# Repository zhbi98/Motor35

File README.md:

# Motor35

转速-扭矩特性步进电机运用普通的开环控制方式在低速和低负载的情况下可以保持较好的控制精度，但随着负载增大或转速度增加会发生丢步，另一个是转速-扭矩特性让步进电机无法在高转速下稳定工作。

## 特性

在低速状态下，步进电机的扭矩特性曲线通常为水平直线，能够提供较高的扭矩。在高速状态下，由于电感的影响，扭矩特性曲线呈指数下降，导致电机的负载能力显著降低。

> **最大扭矩：** 最大扭矩出现在中低转速范围，随着转速的提高，扭矩会逐渐下降。因为在高频率下，电流流动受到绕组电感的影响，导致电流无法达到稳定值，从而扭矩降低。
> 
> **启动扭矩与连续扭矩：** 启动扭矩指在启动时能够提供的最大扭矩，而连续扭矩则指电机持续运行时能够维持的扭矩。随着脉冲频率的增加，启动扭矩和连续扭矩都会下降。

## 闭环

闭环控制是在开环控制的基础上，增加了 **反馈检测环节**（例如在电机轴增加编码器），形成指令-执行-位置检测-修正的闭环逻辑。解决存在的丢步、偏差、抗干扰能力弱问题，还能提升系统和容错能力。

## FOC 控制

混合式步进电机与无刷电机的内在联系（结构定义相似性，工作原理相似性），所以可以用无刷电机 FOC 的驱动思想驱动步进电机。

结构方面：永磁转子+定子绕组的结构，定子方面：两者都有多相绕组（步进电机通常为两相，无刷电机通常为三相），转子方面：都采用永磁材料制造转子磁极，无刷设计：两者都没有电刷和机械换向器，依靠电子换向。

对于两相步进电机，虽然只有两个绕组，但通常两相绕组是正交的，从而可以简化步骤，省略我们的 clarke 变换，所以其余同样可以采用类似的思路进行一个电流环FOC控制。

    电流检测：对 AB 两相电流进行检测
    Park变换：将 AB 轴静止系转换为dq轴旋转坐标系
    PI调节器：对 Id 和 Iq 进行控制
    Invpark变换：讲 dq 轴转换为AB轴
    SVPWM调制: 输出占空比
    双 H桥驱动：驱动我们的步进电机

这些可以整合到一个驱动器中实现，如下图。这就是一体化集成步进电机闭环驱动器。板上集成磁编码器，具有速度，位置，电流闭环控制功能，适用于 3D 打印机，小型机械臂。

## 硬件

(1) 2 相逆变功率级：东芝凌耐压 50V，载流3.5A 的 PWM 斩波式双全桥电机驱动器，内置带低导通电阻的输出MOSFET（基于成本考虑可以选择其他的型号）。

(2) RS485 收发器：TI 德州仪器 SN75176B（基于成本考虑可以选择其他的型号）。

(3) CAN2.0B 收发器：NXP 恩智浦 High-speed CAN transceiver TJA1051（基于成本考虑可以选择其他的型号）。

(4) 磁编码器：MagnTek 麦歌恩 mt6816 单圈绝对式14位编码器，支持最高转速25Krpm。

(6) 主控 MUC 芯片：意法半导体 STM32F103。

## 关于打样

驱动器板 Motor35（PCB 采用 **4 层板** 设计）：[HardWare/kiacd_project](./HardWare/kiacd_project)

如果想自己修改 PCB 需要安装 KiCad（开源的 EDA 工具，也非常易学），官方下载地址： https://www.kicad.org/。

打样制作可以直接进入到下面这两个路径下：

把 Motor35 Gerber 文件夹 [HardWare/Gerber](./Docs/Motor35-PCB/) 压缩为 Motor35.zip，

把这个 .zip 给 PCB 制造厂即可（例如 JLC，**PCB 经过打样验证，可以放心使用**）。

**器件 BOM 目录**：[HardWare/ibom.html](./Docs/Motor35-BOM.csv)（PCB 没器件位号，按网页交互式 BOM 贴片）。

原理图 PDF 目录： [Docs/Motor35-SCH.csv](Docs/Motor35-SCH.pdf)

## 核心固件

固件主要包括几大功能模块：

- hal 驱动：板载的各种硬件驱动比如 USB、Tim、Can、Spi。
- utils 库：STM32 的 Flash 存储接口，Modbus 协议解析库，软定时器组件。
- drivers：ARM的CMSIS驱动，ST官方的HAL库。
- device：电机H桥驱动，编码器驱动和校准，电机控制核心代码，LED 驱动框架 LedMX 和按键驱动 MultiButton。
- main：上层 Can，Rs485 应用控制协议，用于控制同步电机状态/参数，以及用户设置参数保存功能。

## 编译下载

固件没有使用 ARM Keil 开发，而是先用 CMake 构建出 Makefile，然后再用 arm-gcc 编译（可以自己创建 F103 的 Keil 工程，把 Motor35 组织到 Keil 编译）。

Motor35 用的是 VSCode 搭配 OpenOCD 图形化下载调试，需要下载安装下列工具链：

MiniGW： https://sourceforge.net/projects/mingw-w64/files/

arm-gcc ：[Downloads | GNU Arm Embedded Toolchain Downloads – Arm Developer](https://developer.arm.com/downloads/-/gnu-rm)

openOCD：[Download OpenOCD for Windows](https://gnutoolchains.com/arm-eabi/openocd/)

CMake：[Download CMake](https://cmake.org/download/)

VSCode：[https://code.visualstudio.com/](https://code.visualstudio.com/)

> 安装后具体如何配置使用这些工具，篇幅较长不写在这里，我把具体配置使用方法写在这里：[工具链配置使用方法](https://blog.csdn.net/jf_52001760/article/details/126826393)。

**Motor35 编译步骤**：

把 cmake 脚本 CMakeLists.txt 的目录添加到 `1` 这里，如下图。

(2) 在 Firmware 目录下创建 build 目录，并指定到 `2` 这里。

(3) 点击 "Configure"，在弹出面板选择目标工程，如下图。

(5) 在 vscode 的命令行 `cd build` 进入`build/`目录，然后执行 make -j2 即可开始编译。

(6) 使用 openOCD 把 `.elf` 文件下载到 Motor35 硬件，下载方法同样参照 [工具链配置使用方法](https://blog.csdn.net/jf_52001760/article/details/126826393)（PCB 上预留了 SWD 调试接口同时支持固件下载）。

## 电机选型

电机可以在淘宝搜索购买，最好购买低相电阻步进电机（较好的电机的相电阻通常为 2-5 Ohm）。相电阻过高可能导致电机在静止时出现高频震动。

电机机身：28MM，出轴直径：5MM (D轴4.5MM)，出轴长度：22MM
静力矩：0.29 N.m，额定电流：1.5 A，电阻：3.0Ohm/相。

> 要实际测量电机相电阻（万用表接到对应相的两个端子测量），比如购买的步进电机在参数描述中标明的相电阻为 2.2 Ohm，实则实际测出的相电阻高达 29 Ohm
> 
> 

## 编码器安装

在电机轴上安装径向磁铁（用于磁编码器检测），磁铁尺寸 $d=8mm$，$h=2mm$，注意径向磁铁和轴同心度不要过度偏移，让后把驱动器板放到板支架中，用 M3.0 螺丝把驱动器和板定到电机尾部，磁铁与编码器的间隙大概为 $1mm$。

驱动板支架零件目录：[Model](./Model)，把 .step 文件给 3D 打印即可。

## Configuration

固件上已经调试好 Pid 参数，可以适配大多数35步进电机，默认情况下不需要再调试 Pid 电机也能正常工作。Pid 可以用 Can 指令调整（看Can协议部分的说明），方法如下：

- **Kp 的调整**：将 Kd，Ki 置 0，从零开始逐渐增加 Kp，直到系统出现震荡。然后逐渐减小Kp，直到系统不再震荡。Kp 的最终值通常在引起震荡的 Kp 值的 80%-90% 之间。

- **Kd 的调整**：在 Kp 调整稳定后，开始增加 Kd。如果系统在空载时仅需要 Kp，那么在负载情况下可能需要增加 Kd 来减少超调和震荡。

- **Ki 的调整**：如果系统在 Kp 和 Kd 的调整后仍然存在静态误差，可以尝试增加 Ki。但 Ki的值通常很小，需要细致地调整。

配置限制参数，限制参数再 /motor/control_config.h 文件定义，如下。

```c
/********************  硬件配置区  ********************/
#define _Current_Rated_Current  (3000)  /**< 额定电流(mA)*/
#define _Current_Cali_Current   (2000)  /**< 校准电流(mA)*/
/********************  运动参数配置区  ********************/
...
#define _Move_Rated_Speed           ((int32_t)(50 * Move_Pulse_NUM))    /**< (额定转速)(50转每秒)*/
#define _Move_Rated_UpAcc           ((int32_t)(1000 * Move_Pulse_NUM))  /**< (固件额定加速加速度)(1000r/ss)*/
#define _Move_Rated_DownAcc         ((int32_t)(1000 * Move_Pulse_NUM))  /**(固件额定减速加速度)(1000r/ss)*/
#define _Move_Rated_UpCurrentRate   ((int32_t)(20 * _Current_Rated_Current))    /**< (固件额定增流梯度)(20倍额定/s)*/
#define _Move_Rated_DownCurrentRate ((int32_t)(20 * _Current_Rated_Current))    /**< (固件额定减流梯度)(20倍额定/s)*/
```

用户设置在 /main/setup/setup.c 中定义，用户设置参数可以用 Can 指令设置（看Can协议部分的说明）设置后保存在 Flash 掉电保存。

```c
const _setup_t _setup_def = {
    ...
    .can_id = 0x01,
    .home_ofs = 0,
    ...
    .current_down_acc = 2 * 1000, /*(mA/s)*/
    .current_up_acc = 2 * 1000, /*(mA/s)*/
    .current_rated = 1000,
    .cali_current = 2000,
    ...
};
```

## 按键逻辑

(1) 启动停止闭环模式：按键 1 短按一次，启动或停止闭环模式，启动闭环模式的同时会进入默认的模式，例如位置闭环。

(2) 目标清 0：按键 2 短按一次，如果当前控制模式为速度模式，那么按下此时会将目标速度置为 0，位置模式，则将目标位置置为 0。

(3) 电机编码器校准：按键 1 长按两次，校准时电机会慢速正转一圈再反转一圈。

> 按下按键时 LED 跟随闪烁，以指示按键是否响应。

## CAN 协议

一帧 CAN 报文只能传 8 个字节数据，和 11 位的标准 Std-Id，这里把 Std-Id 的低 7 位也用作数据，用来传控制指令字 CMD，控制协议定义如下：

Device Id 占用 4 位，CMD 占用 7 位，协议最多两个参数：参数 1 占用 4 个字节，参数 2 占用 4 个字节。

> 个别协议要两个参数，例如位置控制：设置目标位置和速度限制。

具体指令在[protocols/can_protocol.c](./Firmware/main/protocols/can_protocol.c) 这里定义，具体可以看这个文件，具体控制指令和控制方式查看 [Docs/Protocols](./Docs/Protocols) 目录下相应的协议文档，这里只截取部分。

## 震动问题

注意步进驱动器控制步进电机工作在位置环并要求静止在某个固定位置时可能会出现高频震动的问题。引起高频微弱震动的原因是由于在位置环控制模式下，驱动器为了让让电机接近指定位置而控制电机在齿槽间反复微调而产生震动。

> 这个现象排除驱动器的电路问题（比如焊接的电流采样电阻是否正确等等），磁编码器检测磁铁的安装同心度问题（通常同心度要求不是很高，确保不要过度偏移即可）那有极大的可能是步进电机的相电阻过大导致的，可以更换了其他电机进行测试。

如果更换电机测试后发现同一个闭环步进电机驱动器驱动一个步进电机工作在位置环保持静止时工作正常，而驱动另一个步进电机静止时出现高频震动，那可以肯定就是相电阻过高而导致的。出现震动现象的电机相电阻通常为 10-30 Ohm，而较好电机的相电阻通常为 2-5 Ohm。注意检查电机参数可能的虚标，例如购买的步进电机在参数描述中标明的相电阻为 2.2 Ohm，实则实际测出的相电阻高达 29 Ohm，所以电机出现震动现象和线圈相电阻是有一定关系的。

可以通过修改驱动器程序固件来修复这个问题，修改驱动输出部分，在最终 FOC 输出驱动电流部分添加一个系数即可，通过该系数来调节驱动器 FOC 的输出电流（当然调节电流参数会对最终的扭矩有略微的影响，但并不影响闭环精度），如下图。

## 控制带宽

电机控制速度/位置积分需要精确节拍，电机控制所有逻辑都是在定时器触发的中断中进行，我设置的中断函数频率较高，达到20KHz，可能会导致 main 主循环不执行。

> **20 kHz 中断**：TIM 每 50 μs 触发一次中断。

**电机控制逻辑较多：** 运行时间合计接近或超过 50 μs，会形成中断几乎连轴转、主循环几乎没机会跑”的情况（和芯片主频无关，只要中断内处理的时间超过中断周期时间就会导致 main 函数不执行）。

> 通过 SPI 阻塞读 MT6816，最多 3 次尝试 × 2 次 16bit 传输，再加 16 位奇偶校验循环。SPI 时钟为 9MHz，仅通信就可能 5-15μs。
> 
> 编码器处理、位置/速度估计、多种运行模式下的控制（DCE/PID/电流等）、运动规划、软目标更新、堵转/过载检测等就需要数十μs。

没有具体要求需要多少控制频率，控制制带宽越高，控制越平滑所以默认设定为 20KHz，若控制带宽允许，可把闭环控制改为 10 kHz 或 5 kHz，中断周期变为 100 μs / 200 μs。

> 这里 20 kHz 不是控制带宽的硬性要求，更多是裕量和步进分辨率。

修改控制频率同时改两处：
motion_planner.h 的  CONTROL_FREQUENCY 定义。
修改电机控制运行中断定时器的中断时间。

```c
/****************************************  控制器频率配置区  ****************************************/
#define CONTROL_FREQ_HZ   (20000)                     /**< 控制频率_hz*/
#define CONTROL_PERIOD_US (1000000 / CONTROL_FREQ_HZ) /**< 控制周期_us*/
```

### 评估控制带宽

(1) motor_control.c 涉及的一阶滤波：由 `等效时间常数由 >> 5`（约 32 个采样）决定。20 kHz 时：32 × 50us =1.6 ms 即控制带宽约 100 Hz。对很多应用来说 50 Hz 左右就足够。

(2) 位置/速度环 (DCE、PID 闭环带宽)：这是外环（位置环、速度环），一般做到几十到一两百 Hz 带宽就足够（位置/速度环 -3 dB 带宽）。 

> 常见经验：**采样率 ≥ 10～20 倍闭环带宽**。 
> 若你目标闭环带宽在 100～200 Hz，**5 kHz 已经够用，2 kHz 是底线**。

(3) FOC/电流指令：由 TB67H450 等驱动接收，5～10 kHz 更新电流给定对多数应用足够。

(4) 运动规划：用 CONTROL_FREQUENCY 做离散积分，频率高一点更平滑，但 5～10 kHz 通常足够平滑。

(5) 控制更新频率：下限约 2～5 kHz（再低速度估计和环路的相位裕量会变差）。推荐 5～10 kHz 在保证控制性能的同时，能给主循环留出明显时间。在需要 **极高步进率** 或 **尽量小的相位延迟** 时才必要 20 kHz。

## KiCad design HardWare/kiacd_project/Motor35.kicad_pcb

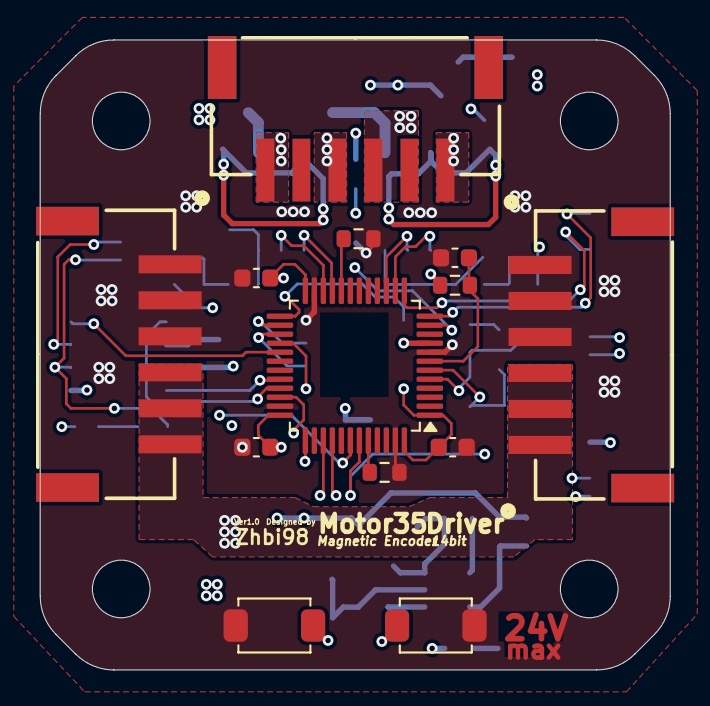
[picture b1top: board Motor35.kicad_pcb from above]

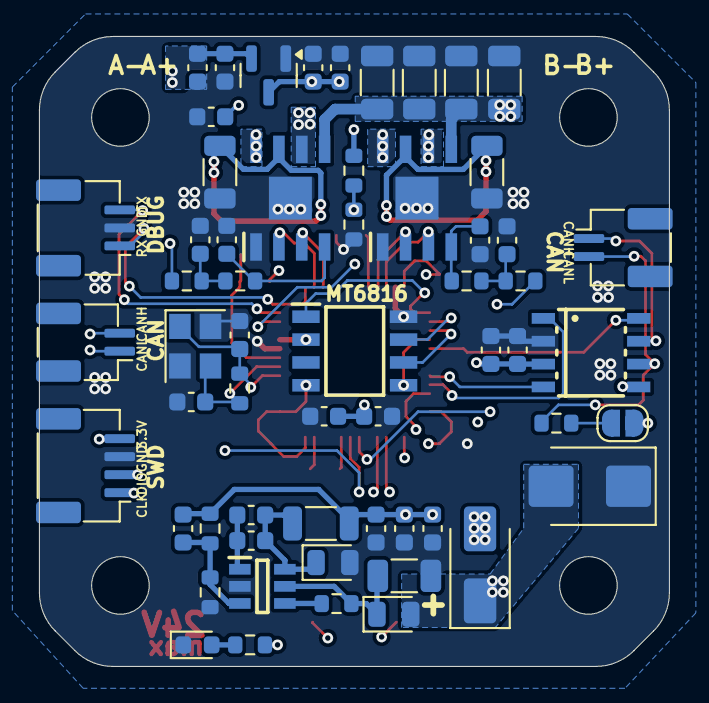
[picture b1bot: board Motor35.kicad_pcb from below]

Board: 4 copper layers, 35.0 x 35.0 mm, 71 parts (58 on the bottom side), 49 nets.

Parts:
C1, C3, C5, C7, C10, C11, C16: 0.1uF; C_0603_1608Metric
C2, C6: 22pF; C_0603_1608Metric
C4, C8, C17, C26, C31: 10uF; C_0603_1608Metric
C12, C13, C14, C15: 100nF (104) 10% 50V; C_0603_1608Metric
C18: 100pF(101) 50V; C_0603_1608Metric
C19, C20: 100nF(104) 50V; C_0603_1608Metric
C21: 100nF104; C_0603_1608Metric
C22: 4.7uF(475) 50V; C_1206_3216Metric
C23: 10uF(106); C_0603_1608Metric
C24: 47uF(106); C_0603_1608Metric
C27, C28, C29, C30: 100uF 50V; C_1206_3216Metric
C32: 100nF; C_0603_1608Metric
D1: RED LED; LED_0603_1608Metric
D2, D3: B5819WS; D_0805_2012Metric
D4: SS54; D_SMA
D5: SMBJ28CA; D_SMB
IC1, IC2: TB67H450FNG,EL; SOIC-8_L4.8-W5.8-P1.27_TB67H450FNG
IC3: MT6816; SOIC-8_L4.7-W5.8-P1.27_MT6816
IC4: ME3116AM6G; SOT-23-6_L2.7-W2.2-P0.95_ME3116AM6G
J1: DBUG; CONN-SMD_1x3P-P1.0-H_WAFER-SH1.0-3PWB
J2: SWD; CONN-SMD_1x4P-P1.0-H_WAFER-SH1.0-4PWB
J3, J7: CAN_BUS; CONN-SMD_1x2P-P1.0-H_WAFER-SH1.0-2PWB
J4: MOTOR; CONN-SMD_1x6P-P2.0-H_WAFER-PH2.0-6PWB
J5, J6: POWER IN; CONN-SMD_1x6P-P2.0-H_WAFER-PH2.0-6PWB
JP1: Jump; SolderJumper-2_P1.3mm_Open_RoundedPad1.0x1.5mm
L1: FCI3216-6R8 6.8uH; L_1206_3216Metric
R1: 10M; R_0603_1608Metric
R2: 3.3K; R_0603_1608Metric
R5, R9, R10: 10K; R_0603_1608Metric
R8: 1k; R_0603_1608Metric
R11, R12, R13, R14: 1KΩ (1001) ±1%; R_0603_1608Metric
R15, R16: 0.1Ω (R100) ±1%; R_1206_3216Metric
R17: 1.91k(1901); R_0603_1608Metric
R18: 10k(1002); R_0603_1608Metric
R19: 1M; R_0603_1608Metric
R22: 120R; R_0603_1608Metric
S1, S2: KEY-PB_4P_MIN; KEY-SMD_2P_L4.0-W3.0-V_K2-1807SN-A3DW-06
TH1: 10K; R_0603_1608Metric
U1: XC6206P332MR; SOT-23
U2: STM32F103CBTx; LQFP-48_7x7mm_P0.5mm
U3: TJA1051T; SOT96_L5.0-W4.0-P1.27_TJA1051
Y1: 3225 8M 12PF 10PPM; Crystal_SMD_3225-4Pin_3.2x2.5mm

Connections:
+3.3V: C3.1, C5.1, C7.1, C8.1, C10.1, C16.1, C17.1, IC3.2 (HVPP), IC3.4 (VDD), J2.4, R5.1, R8.1, TH1.1, U1.2 (VO), U2.1 (VBAT), U2.9 (VDDA), U2.24 (VDD), U2.36 (VDD), U2.48 (VDD), U3.5 (VI/O)
+5V: C1.1, C4.1, C18.1, C21.1, C23.1, C24.1, C31.1, C32.1, L1.2, R18.1, U1.3 (VI), U3.3 (VCC)
+24V: D4.2 (A), J5.4, J5.5, J5.6, J6.1, J6.2, J6.3
/CAN_RX: U2.32 (PA11), U3.4 (RXD)
/CAN_SILENT: U2.29 (PA8), U3.8 (S)
/CAN_TX: U2.33 (PA12), U3.1 (TXD)
/DEBUG_RX: J1.1, U2.13 (PA3)
/DEBUG_TX: J1.3, U2.12 (PA2)
/H_BRID/MOTOR_OUT_A+: IC1.6 (OUT1), J4.3
/H_BRID/MOTOR_OUT_A-: IC1.8 (OUT2), J4.1
/H_BRID/MOTOR_OUT_B+: IC2.6 (OUT1), J4.6
/H_BRID/MOTOR_OUT_B-: IC2.8 (OUT2), J4.4
/H_BRID/VREF_A: C14.1, IC1.4 (VREF), R13.2
/H_BRID/VREF_B: C15.1, IC2.4 (VREF), R14.2
/KEY1: S1.2, U2.39 (PB3)
/KEY2: S2.2, U2.40 (PB4)
/MT6816_CS: IC3.1 (CSN), U2.25 (PB12)
/MT6816_MISO: IC3.6 (B/V), U2.27 (PB14)
/MT6816_MOSI: IC3.5 (A/U), U2.28 (PB15)
/MT6816_SCK: IC3.7 (Z/W), U2.26 (PB13)
/OSC_IN: C2.1, R1.2, U2.5 (PD0), Y1.1
/OSC_OUT: C6.1, R1.1, U2.6 (PD1), Y1.3
/PORT/_CAN_H: J3.2, J7.1, JP1.1 (A), U3.7 (CANH)
/PORT/_CAN_L: J3.1, J7.2, R22.2, U3.6 (CANL)
/SWD_CLK: J2.1, U2.37 (PA14)
/SWD_DIO: J2.2, U2.34 (PA13)
/TB_IN_AM: IC1.2 (IN2), U2.14 (PA4)
/TB_IN_AP: IC1.3 (IN1), U2.15 (PA5)
/TB_IN_BM: IC2.2 (IN2), U2.21 (PB10)
/TB_IN_BP: IC2.3 (IN1), U2.22 (PB11)
/TB_IN_PWM_A: R11.1, U2.43 (PB7)
/TB_IN_PWM_B: R12.1, U2.42 (PB6)
/TB_Temp: C26.1, R2.2, TH1.2, U2.11 (PA1)
/nRST: C11.1, R5.2, U2.7 (NRST)
GND: C1.2, C2.2, C3.2, C4.2, C5.2, C6.2, C7.2, C8.2, C10.2, C11.2, C12.2, C13.2, C14.2, C15.2, C16.2, C17.2, C21.2, C22.2, C23.2, C24.2, C26.2, C27.2, C28.2, C29.2, C30.2, C31.2, C32.2, D1.1 (K), D2.2 (A), D5.1 (A1), IC1.1 (GND), IC1.9 (EP), IC2.1 (GND), IC2.9 (EP), IC3.8 (GND), IC4.2 (GND), J1.2, J2.3, J5.1, J5.2, J5.3, J6.4, J6.5, J6.6, R2.1, R9.2, R10.2, R15.2, R16.2, R17.2, S1.1, S2.1, U1.1 (GND), U2.8 (VSSA), U2.23 (VSS), U2.35 (VSS), U2.47 (VSS), U3.2 (GND), Y1.2, Y1.4
unnamed: C12.1, R11.2, R13.1
unnamed: C13.1, R12.2, R14.1
unnamed: D1.2 (A), R8.2
unnamed: C19.2, C20.2, D2.1 (K), IC4.6 (SW), L1.1
unnamed: C22.1, D3.1 (K), IC4.5 (VIN), R19.2
unnamed: IC1.7 (RS), R15.1
unnamed: IC2.7 (RS), R16.1
unnamed: C19.1, C20.1, IC4.1 (BST)
unnamed: IC4.4 (EN), R19.1
unnamed: C18.2, IC4.3 (FB), R17.1, R18.2
unnamed: JP1.2 (B), R22.1
unnamed: R10.1, U2.44 (BOOT0)
unnamed: R9.1, U2.20 (PB2)
VCC: C27.1, C28.1, C29.1, C30.1, D3.2 (A), D4.1 (K), D5.2 (A2), IC1.5 (VM), IC2.5 (VM)

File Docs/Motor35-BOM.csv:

"Reference","Value","Datasheet","Footprint","Qty","DNP"
"C1,C3,C5,C7,C10,C11,C16","0.1uF","~","Capacitor_SMD:C_0603_1608Metric","7",""
"C2,C6","22pF","~","Capacitor_SMD:C_0603_1608Metric","2",""
"C4,C8,C17,C26,C31","10uF","~","Capacitor_SMD:C_0603_1608Metric","5",""
"C12,C13,C14,C15","100nF (104) 10% 50V","~","Capacitor_SMD:C_0603_1608Metric","4",""
"C18","100pF(101) 50V","~","Capacitor_SMD:C_0603_1608Metric","1",""
"C19,C20","100nF(104) 50V","~","Capacitor_SMD:C_0603_1608Metric","2",""
"C21","100nF104","~","Capacitor_SMD:C_0603_1608Metric","1",""
"C22","4.7uF(475) 50V","~","Capacitor_SMD:C_1206_3216Metric","1",""
"C23","10uF(106)","~","Capacitor_SMD:C_0603_1608Metric","1",""
"C24","47uF(106)","~","Capacitor_SMD:C_0603_1608Metric","1",""
"C27,C28,C29,C30","100uF 50V","~","Capacitor_SMD:C_1206_3216Metric","4",""
"C32","100nF","~","Capacitor_SMD:C_0603_1608Metric","1",""
"D1","RED LED","~","LED_SMD:LED_0603_1608Metric","1",""
"D2,D3","B5819WS","http://www.vishay.com/docs/85622/1n914.pdf","Diode_SMD:D_0805_2012Metric","2",""
"D4","SS54","http://www.vishay.com/docs/85622/1n914.pdf","Diode_SMD:D_SMA","1",""
"D5","SMBJ28CA","https://www.vishay.com/docs/88301/15ke.pdf","Diode_SMD:D_SMB","1",""
"IC1,IC2","TB67H450FNG,EL","http://toshiba.semicon-storage.com/info/docget.jsp?did=65346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","3rd_Driver_Motor:SOIC-8_L4.8-W5.8-P1.27_TB67H450FNG","2",""
"IC3","MT6816","http://www.magntek.com.cn/upload/MT6816_Rev.2.0.pdf","3rd_Sensor_Encoder:SOIC-8_L4.7-W5.8-P1.27_MT6816","1",""
"IC4","ME3116AM6G","https://componentsearchengine.com/Datasheets/1/ME3116AM6G.pdf","3rd_Converter_DCDC:SOT-23-6_L2.7-W2.2-P0.95_ME3116AM6G","1",""
"J1","DBUG","","3rd_Connector_JST_SMD:CONN-SMD_1x3P-P1.0-H_WAFER-SH1.0-3PWB","1",""
"J2","SWD","","3rd_Connector_JST_SMD:CONN-SMD_1x4P-P1.0-H_WAFER-SH1.0-4PWB","1",""
"J3,J7","CAN_BUS","","3rd_Connector_JST_SMD:CONN-SMD_1x2P-P1.0-H_WAFER-SH1.0-2PWB","2",""
"J4","MOTOR","","3rd_Connector_JST_SMD:CONN-SMD_1x6P-P2.0-H_WAFER-PH2.0-6PWB","1",""
"J5,J6","POWER IN","","3rd_Connector_JST_SMD:CONN-SMD_1x6P-P2.0-H_WAFER-PH2.0-6PWB","2",""
"JP1","Jump","~","Jumper:SolderJumper-2_P1.3mm_Open_RoundedPad1.0x1.5mm","1",""
"L1","FCI3216-6R8  6.8uH","~","Inductor_SMD:L_1206_3216Metric","1",""
"R1","10M","~","Resistor_SMD:R_0603_1608Metric","1",""
"R2","3.3K","~","Resistor_SMD:R_0603_1608Metric","1",""
"R5,R9,R10,TH1","10K","~","Resistor_SMD:R_0603_1608Metric","4",""
"R8","1k","~","Resistor_SMD:R_0603_1608Metric","1",""
"R11,R12,R13,R14","1KΩ (1001) ±1%","~","Resistor_SMD:R_0603_1608Metric","4",""
"R15,R16","0.1Ω (R100) ±1%","~","Resistor_SMD:R_1206_3216Metric","2",""
"R17","1.91k(1901)","~","Resistor_SMD:R_0603_1608Metric","1",""
"R18","10k(1002)","~","Resistor_SMD:R_0603_1608Metric","1",""
"R19","1M","~","Resistor_SMD:R_0603_1608Metric","1",""
"R22","120R","~","Resistor_SMD:R_0603_1608Metric","1",""
"S1,S2","KEY-PB_4P_MIN","","3rd_Button_Switch_SMD:KEY-SMD_2P_L4.0-W3.0-V_K2-1807SN-A3DW-06","2",""
"U1","XC6206P332MR","https://www.torexsemi.com/file/xc6206/XC6206.pdf","Package_TO_SOT_SMD:SOT-23","1",""
"U2","STM32F103CBTx","https://www.st.com/resource/en/datasheet/stm32f103cb.pdf","Package_QFP:LQFP-48_7x7mm_P0.5mm","1",""
"U3","TJA1051T","","3rd_Interface_CAN:SOT96_L5.0-W4.0-P1.27_TJA1051","1",""
"Y1","3225 8M 12PF 10PPM","~","Crystal:Crystal_SMD_3225-4Pin_3.2x2.5mm","1",""

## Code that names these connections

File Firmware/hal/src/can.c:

/**
 * For example, when the official PWM 
 * peripheral initialization function is called, 
 * the initialization function will check 
 * whether the corresponding named MSP 
 * function exists, and if it exists, it will 
 * be called.
 * Therefore, for MCU firmware libraries that 
 * do not support this feature, they can 
 * implement a similar mechanism by 
 * themselves.
 */

/**
 * @file can.c
 *
 */

/*********************
 *      INCLUDES
 *********************/

#include "stm32f1xx_hal.h"
#include "setup.h"
#include "can.h"

/*********************
 *      DEFINES
 *********************/

/**********************
 *      TYPEDEFS
 **********************/

/*CAN Tx message header structure definition.*/
CAN_TxHeaderTypeDef TxHeader = {0};
/*CAN Rx message header structure definition.*/
CAN_RxHeaderTypeDef RxHeader = {0};

CAN_HandleTypeDef hcan = {0};

uint8_t TxData[8] = {0};
uint8_t RxData[8] = {0};

uint32_t TxMailbox = 0;

/**********************
 *   GLOBAL FUNCTIONS
 **********************/

/**
 * @brief  Initializes the CAN peripheral according to the specified
 *         parameters in the CAN_InitStruct.
 * @param  hcan pointer to a CAN_HandleTypeDef structure that contains
 *         the configuration information for the specified CAN.
 * @retval HAL status
 */
void x35_can_init()
{
    /* USER CODE BEGIN CAN_Init 0 */

    /* USER CODE END CAN_Init 0 */

    /* USER CODE BEGIN CAN_Init 1 */

    /* USER CODE END CAN_Init 1 */

    hcan.Instance = CAN1;
    hcan.Init.Prescaler = 8; /*36MHz/(5tq+3tq+1tq)/prescaler = 500KHz*/
    hcan.Init.Mode = CAN_MODE_NORMAL;
    hcan.Init.SyncJumpWidth = CAN_SJW_1TQ;
    hcan.Init.TimeSeg1 = CAN_BS1_5TQ;
    hcan.Init.TimeSeg2 = CAN_BS2_3TQ;
    hcan.Init.TimeTriggeredMode = DISABLE;
    hcan.Init.AutoBusOff = DISABLE;
    hcan.Init.AutoWakeUp = DISABLE;
    hcan.Init.AutoRetransmission = DISABLE;
    hcan.Init.ReceiveFifoLocked = DISABLE;
    hcan.Init.TransmitFifoPriority = DISABLE;
    if (HAL_CAN_Init(&hcan) != HAL_OK)
    {
        Error_Handler();
    }
    /* USER CODE BEGIN CAN_Init 2 */
    CAN_FilterTypeDef sFilterConfig;
    /*Filter one (stack light blink)*/
    sFilterConfig.FilterBank = 0;
    sFilterConfig.FilterMode = CAN_FILTERMODE_IDMASK;
    sFilterConfig.FilterScale = CAN_FILTERSCALE_32BIT;
    sFilterConfig.FilterIdHigh = 0x0000;
    sFilterConfig.FilterIdLow = 0x0000;
    sFilterConfig.FilterMaskIdHigh = 0x0000;
    sFilterConfig.FilterMaskIdLow = 0x0000;
    sFilterConfig.FilterFIFOAssignment = CAN_RX_FIFO0;
    sFilterConfig.FilterActivation = ENABLE;
    sFilterConfig.SlaveStartFilterBank = 14;
    if (HAL_CAN_ConfigFilter(&hcan, 
        &sFilterConfig) != HAL_OK)
    {
        /*Filter configuration Error*/
        Error_Handler();
    }

    HAL_CAN_Start(&hcan); /*Start CAN*/

    HAL_CAN_ActivateNotification(&hcan,
        CAN_IT_TX_MAILBOX_EMPTY |
        CAN_IT_RX_FIFO0_MSG_PENDING | CAN_IT_RX_FIFO1_MSG_PENDING |
        /*We probably only want this*/
        CAN_IT_RX_FIFO0_FULL | CAN_IT_RX_FIFO1_FULL |
        CAN_IT_RX_FIFO0_OVERRUN | CAN_IT_RX_FIFO1_OVERRUN |
        CAN_IT_WAKEUP | CAN_IT_SLEEP_ACK |
        CAN_IT_ERROR_WARNING | CAN_IT_ERROR_PASSIVE |
        CAN_IT_BUSOFF | CAN_IT_LAST_ERROR_CODE |
        CAN_IT_ERROR);

    /* Configure Transmission process */
    TxHeader.StdId = 0x01/*canNodeId*/;
    TxHeader.ExtId = 0x00;
    TxHeader.RTR = CAN_RTR_DATA;
    TxHeader.IDE = CAN_ID_STD;
    TxHeader.DLC = 8;
    TxHeader.TransmitGlobalTime = DISABLE;
    /* USER CODE END CAN_Init 2 */
}

/**
 * @brief  Initializes the GPIOx peripheral according to the specified parameters in the GPIO_Init.
 * @param  GPIOx: where x can be (A..G depending on device used) to select the GPIO peripheral
 * @param  GPIO_Init: pointer to a GPIO_InitTypeDef structure that contains
 *         the configuration information for the specified GPIO peripheral.
 * @retval None
 */
void HAL_CAN_MspInit(CAN_HandleTypeDef *canHandle)
{
    GPIO_InitTypeDef GPIO_InitStruct = {0};

    if(canHandle->Instance == CAN1) {
        /* USER CODE BEGIN CAN1_MspInit 0 */

        /* USER CODE END CAN1_MspInit 0 */
        /* CAN1 clock enable */
        __HAL_RCC_CAN1_CLK_ENABLE();
        __HAL_RCC_AFIO_CLK_ENABLE();
        __HAL_RCC_GPIOA_CLK_ENABLE();
        /**CAN GPIO Configuration
        PA11 ------> CAN_RX
        PA12 ------> CAN_TX
        */
        GPIO_InitStruct.Pin = GPIO_PIN_11;
        GPIO_InitStruct.Mode = GPIO_MODE_INPUT;
        GPIO_InitStruct.Pull = GPIO_NOPULL;
        HAL_GPIO_Init(GPIOA, &GPIO_InitStruct);

        GPIO_InitStruct.Pin = GPIO_PIN_12;
        GPIO_InitStruct.Mode = GPIO_MODE_AF_PP;
        GPIO_InitStruct.Speed = GPIO_SPEED_FREQ_HIGH;
        HAL_GPIO_Init(GPIOA, &GPIO_InitStruct);

        /*PA11 PA12 defaults to CAN port and no remapping is required*/
        /*__HAL_AFIO_REMAP_CAN1_2();*/

        /* CAN1 interrupt Init */
        HAL_NVIC_SetPriority(USB_HP_CAN1_TX_IRQn, 0/*3*/, 0);
        HAL_NVIC_EnableIRQ(USB_HP_CAN1_TX_IRQn);

        HAL_NVIC_SetPriority(USB_LP_CAN1_RX0_IRQn, 0/*3*/, 0);
        HAL_NVIC_EnableIRQ(USB_LP_CAN1_RX0_IRQn);

        HAL_NVIC_SetPriority(CAN1_RX1_IRQn, 0/*3*/, 0);
        HAL_NVIC_EnableIRQ(CAN1_RX1_IRQn);

        HAL_NVIC_SetPriority(CAN1_SCE_IRQn, 0/*3*/, 0);
        HAL_NVIC_EnableIRQ(CAN1_SCE_IRQn);
        /* USER CODE BEGIN CAN1_MspInit 1 */

        /* USER CODE END CAN1_MspInit 1 */
    }
}

/**
  * @brief  De-initializes the GPIOx peripheral registers to their default reset values.
  * @param  GPIOx: where x can be (A..G depending on device used) to select the GPIO peripheral
  * @param  GPIO_Pin: specifies the port bit to be written.
  *         This parameter can be one of GPIO_PIN_x where x can be (0..15).
  * @retval None
  */
void HAL_CAN_MspDeInit(CAN_HandleTypeDef* canHandle)
{
    if(canHandle->Instance == CAN1) {
        /* USER CODE BEGIN CAN1_MspDeInit 0 */

        /* USER CODE END CAN1_MspDeInit 0 */
        /* Peripheral clock disable */
        __HAL_RCC_CAN1_CLK_DISABLE();

        /**CAN GPIO Configuration
        PA11     ------> CAN_RX
        PA12     ------> CAN_TX
        */
        HAL_GPIO_DeInit(GPIOA, GPIO_PIN_11 | GPIO_PIN_12);

        /* CAN1 interrupt Deinit */
        HAL_NVIC_DisableIRQ(USB_HP_CAN1_TX_IRQn);
        HAL_NVIC_DisableIRQ(USB_LP_CAN1_RX0_IRQn);
        HAL_NVIC_DisableIRQ(CAN1_RX1_IRQn);
        HAL_NVIC_DisableIRQ(CAN1_SCE_IRQn);
        /* USER CODE BEGIN CAN1_MspDeInit 1 */

        /* USER CODE END CAN1_MspDeInit 1 */
    }
}

/* USER CODE BEGIN 1 */

/**
  * @brief  Add a message to the first free Tx mailbox and activate the
  *         corresponding transmission request.
  * @param  hcan pointer to a CAN_HandleTypeDef structure that contains
  *         the configuration information for the specified CAN.
  * @param  pHeader pointer to a CAN_TxHeaderTypeDef structure.
  * @param  aData array containing the payload of the Tx frame.
  * @param  pTxMailbox pointer to a variable where the function will return
  *         the TxMailbox used to store the Tx message.
  *         This parameter can be a value of @arg CAN_Tx_Mailboxes.
  * @retval HAL status
  */
void CAN_Send(CAN_TxHeaderTypeDef * pHeader, uint8_t * data)
{
    if (HAL_CAN_AddTxMessage(&hcan, pHeader, 
        data, &TxMailbox) != HAL_OK)
    {
        Error_Handler();
    }
}

/**
  * @brief  Get an CAN frame from the Rx FIFO zone into the message RAM.
  * @param  hcan pointer to an CAN_HandleTypeDef structure that contains
  *         the configuration information for the specified CAN.
  * @param  RxFifo Fifo number of the received message to be read.
  *         This parameter can be a value of @arg CAN_receive_FIFO_number.
  * @param  pHeader pointer to a CAN_RxHeaderTypeDef structure where the header
  *         of the Rx frame will be stored.
  * @param  aData array where the payload of the Rx frame will be stored.
  * @retval HAL status
  */
void HAL_CAN_RxFifo0MsgPendingCallback(CAN_HandleTypeDef* hcan)
{
    /* Get RX message */
    if (HAL_CAN_GetRxMessage(hcan, CAN_RX_FIFO0, &RxHeader, RxData) != HAL_OK)
    {
        /* Reception Error */
        Error_Handler();
    }

    /**
     * CAN is configured in identifier masking mode, 
     * all packets are received, and the corresponding ID packets are filtered 
     * out in the form of software masks, which is commonly 
     * referred to as software filtering
     */

    uint8_t id = (RxHeader.StdId >> 7); // 4Bits ID & 7Bits Msg
    uint8_t cmd = RxHeader.StdId & 0x7F; // 4Bits ID & 7Bits Msg
    uint8_t canNodeId = _setup.can_id;
    if (id == 0 || id == canNodeId)
    {
        /*OnCanCmd(cmd, RxData, RxHeader.DLC);*/
        extern void dev_can_cmd(uint8_t _cmd, uint8_t * _data, uint32_t _len);
        dev_can_cmd(cmd, RxData, RxHeader.DLC);
    }
}
/* USER CODE END 1 */

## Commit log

2025-03-30 更新问题说明
2025-04-09 移除ADC,DMA中断，减小ARM芯片负载
2025-04-14 位置环控制时调节到达目标位置的额定速度和时间，新额定速度，过程时间未生效问题
2025-07-20 Can not set the acceleration, otherwise the mode switching speed can not be limited in time.
    Can not set the acceleration, otherwise the mode switching speed can not be limited in time.
2025-08-12 增加设备串口输出流__fputs接口
2026-03-07 完善README说明文档
2026-03-07 motor_control中断频率较高达到20KHz,导致main主循环不执行,导致运行转速不准
